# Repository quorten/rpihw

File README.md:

`rpihw` -- My First Raspberry Pi Hardware Project
=================================================

Background Info
---------------

This is my first large-scale Raspberry Pi hardware project.  The
original overly large goals of my Raspberry Pi hardware project was to
have one Raspberry Pi hardware device with all imaginable peripheral
interfaces I could ever conceivably need, so I could just plug in what
I need for a particular session.  But, since that's too large sweeping
of a goal to achieve... let's simply state what my actual design does.

This is my first iteration at designing a Raspberry Pi SPI devices
board.  The path to this real implementation started out by playing
with the Texas Instruments SN74HC595N shift register from an Arduino
parts pack.  Cool, it's an integrated circuit, but dang,
intimidating... how am I going to program this shift register?  But
then, I wired up 4 tactile switches, 1 pull-up resistor, 3 pull-down
resistors, and a 7-segment LED with decimal point.  Then... wow, I was
hooked, it's so easy and simple, and it could in theory be
daisy-chained to control an unlimited number of devices... limited
only by signal timing constraints.

I also went reading in more detail about SPI (Serial Peripheral
Interface), and I realized, hey, SPI is really just a glorified
interface to a plain old shift register integrated circuit.  I should
really try making a board that exposes some plain old shift registers
to Raspberry Pi as SPI devices.  So, that's what I started out doing.

What the main board does
------------------------

1. SPI Display/Keypad controller: 8-bit input word, 8-bit output word
   SPI device.  You program an 8-bit shift register that controls the
   display contents of one 7-segment LED digit, including decimal
   point.  An internal counter circuit automatically advances the
   current digit, so that when you write on the next cycle, you will
   set the contents of the next digit.  The input is the contents of
   one row (or column, depending on wiring) of the keyboard.  By
   reading/writing in rapid succession, you can control an 8-digit
   multiplexed LED digit display and read a 64-key keyboard.

   Technically, with one more demultiplexer chip, the circuit could
   easily be extended to a 16-digit display and a 128-key keyboard.

2. SPI motor controller: 8-bit output word SPI device.  Since this is
   an asymmetric SPI device, you must take corresponding caution when
   daisy-chaining it.  Two L293D motor controllers with some glue
   logic chips to reduce the number of bits to program them.  Can
   control up to 4 DC motors or 8 solenoids.  2 bits indicate one of 4
   states for each motor: (0) coast, (1) forward, (2) reverse, (3)
   brake.

3. Miscellaneous GPIO device control: Other single pin connections for
   controlling some LEDs, a PWM buzzer, and an arbitrary
   higher-powered device.

Of course, there is still more plenty of expansion capability for
connecting off-board SPI devices, provided that the distance is not so
long that capacitance and signaling delays becomes a problem.  In
theory, UART transceivers are an easy and cheap way to connect distant
devices to a daisy-chained SPI bus.

Oh, and I didn't even cover I2C yet.  Sure, you can populate
connectors and solder on headers for modular connection to that as you
please.

What the auxiliary boards do
----------------------------

* SPI Debug Board: a fancier, more formal recreation of my original
  breadboard design for playing with the shift register, give yourself
  a nice permanent fixture for those four buttons and the official
  connector interface I use for my SPI devices on this board design.
  Also, this is a great first time perboard project to build.

* Additional I/O connectors and device interface board: Everything
  that didn't fit on the first Eurocard perfboard that I bought, I put
  on a piece of my own "cardboard circuit board" when building the
  perfboard prototype.

Credits
-------

* Digi-Key: I used Digi-Key to prepare the Bill of Materials from my
  initial design specifications.  Also, I used the Digi-Key KiCad
  parts library when designing the formal schematics in KiCad.

* KiCad: The formal design documentation for this project is drafted
  in KiCad.  That is, anything that is not specified straight up in
  generic documentation formats like Markdown, HTML, SVG graphics,
  PDFs, spreadsheets, etc.

* UltraLibrarian: I used UltraLibrarian to get KiCad library files for
  some of the Digi-Key parts.  It's not great, and had I known in
  advance, I should have used the Digi-Key KiCad parts library for as
  many of the parts that were available over there.

* KiBoM: Some of the early versions of KiCad (if you're stuck using an
  older Debian-based distro for various odd reasons) don't have very
  nice BOM generators bundled by default, KiBoM is a fairly nice BOM
  generator to use in these cases.  It might also provide some other
  useful advanced features not in the BOM generators in the newer
  KiCad versions.

* Icarus Verilog: Open Hardware tools are not as integrated as they
  could or should be... it seems the best way to simulate digital glue
  logic is to code it up in Verilog.  Of course, this doesn't provide
  simulation for any of the analog glue connections, I'm just relying
  on careful eyeing of the schematics and best effort with my current,
  somewhat limited, design experience for that one.

N.B.: Modern versions of KiCad don't have the simple internal
autorouter, it wasn't forward ported when was Pcbnew was extensively
refactored.  That's another benefit of the older versions, if you just
want to play around with simple auto-routing because you can.  I'm
still developing this project in KiCad 4 rather than the latest
version.

Copyright Info
--------------

The rest of this project, i.e. the board design itself excluding the
library files, is in public domain via the UNLICENSE.

The Digi-Key KiCad parts library uses the Creative Commons
Share-Alike, with a special exemption that tantamounts to "fair use"
under copyright law if only bits and pieces are used for a particular
project, as opposed to most of the library.

The UltraLibrarian library parts are under proprietary copyright, but
also come with a special exemption that tantamounts to "fair use"
under copyright law if only bits and pieces are used for a particular
project, as opposed to most of the library.

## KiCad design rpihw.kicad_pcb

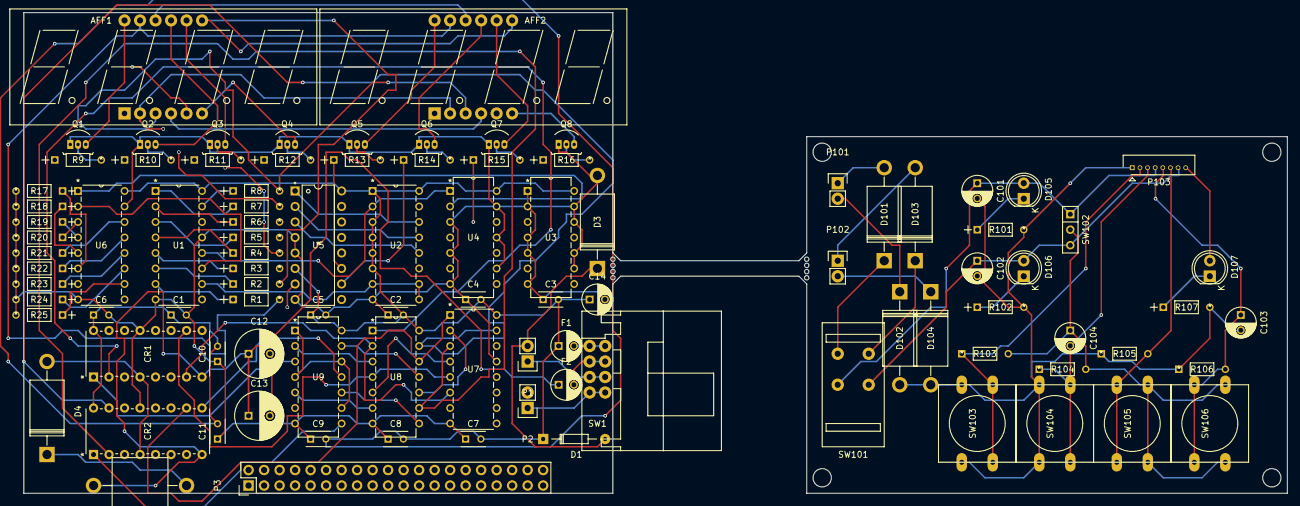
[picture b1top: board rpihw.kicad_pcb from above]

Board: 4 copper layers, 207.0 x 78.7 mm, 101 parts (0 on the bottom side), 101 nets.

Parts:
AFF1, AFF2: LDQ-N516RI; Cx56-12
C1, C2, C3, C4, C5, C6, C7, C8, C9, C10, C11: 100nF; C_Rect_L4_W2.5_P2.5
C12, C13: 220uF; C_Radial_D8_L11.5_P3.5
C14, C101, C102: 100uF; C_Radial_D5_L11_P2.5
C103: 10uF; C_Radial_D5_L11_P2.5
C104: 1uF; C_Radial_D5_L11_P2.5
CR1, CR2: L293D; PowerDIP-16
D1: 5V 9.2V; Diode_DO-35_SOD27_Horizontal_RM10
D2: 33V 53.3V; Diode_R-6_Horizontal_Unpol_RM15
D3, D4, D101, D102, D103, D104: 5A; Diode_DO-201AD_Horizontal_RM15
D105, D107: LED RED; LED-5MM
D106: LED YELW; LED-5MM
F1: 16V 2A; C_Radial_D5_L11_P2.5
F2: 60V 1.1A; C_Radial_D5_L11_P2.5
MH101, MH102, MH103, MH104: Mounting_Hole; MountingHole_3mm
P1, P2, P101, P102: CONN_01X02; Pin_Header_Straight_1x02
P3: CONN_02X20; Pin_Header_Straight_2x20
P103: CONN_01X08; Connector_Molex_PicoBlade_53047-0810
Q1, Q2, Q3, Q4, Q5, Q6, Q7, Q8: 2N3904BU; TO-92-3
R1, R2, R3, R4, R5, R6, R7, R8, R101, R102, R107: 220; STA_RNMF14
R9, R10, R11, R12, R13, R14, R15, R16: 4.7K; STA_RNMF14
R17, R18, R19, R20, R21, R22, R23, R24, R25: 51K; STA_RNMF14
R103, R104, R105: 10K; STA_RNMF14_STP
R106: 1K; STA_RNMF14_STP
SW1: DPST 6A; Hack_S201
SW101: DPST 4A; Hack_L201
SW102: SPDT 200mA; SW_Micro_SPST
SW103, SW104, SW105, SW106: SW_PUSH; SW_PUSH-12mm
U1, U7: SN74HC595N; N16
U2: SN74HC161N; N16
U3, U9: SN74HC08N; N14
U4: SN74HC04N; N14
U5: CD74HC238E; N0016A
U6: SN74HC165N; N16
U8: SN74HC32N; N14

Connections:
/RPI SPI BOARD DIP/GND_MTR: C12.2, C13.2, CR1.4, CR2.4, D4.2
/SPI 7-SEG DPLY KEYPAD CTL DIP/*RST: U1.10, U2.7, U2.9, U2.10
/SPI 7-SEG DPLY KEYPAD CTL DIP/GND: C1.2, C2.1, C3.1, C4.1, C5.2, C6.2, C7.1, C8.1, C9.1, C10.1, C11.1, C14.2, CR1.13, CR2.13, D3.2, Q1.1, Q2.1, Q3.1, Q4.1, Q5.1, Q6.1, Q7.1, Q8.1, R17.2, R18.2, R19.2, R20.2, R21.2, R22.2, R23.2, R24.2, R25.2, U1.8, U1.13, U2.8, U3.1, U3.2, U3.4, U3.5, U3.7, U3.9, U3.10, U3.12, U3.13, U4.3, U4.5, U4.7, U4.9, U4.11, U4.13, U5.4, U5.5, U5.8, U6.8, U6.15, U7.8, U7.13, U8.7, U9.7
/SPI 7-SEG DPLY KEYPAD CTL DIP/IN1: R24.1, U6.11
/SPI 7-SEG DPLY KEYPAD CTL DIP/IN2: R23.1, U6.12
/SPI 7-SEG DPLY KEYPAD CTL DIP/IN3: R22.1, U6.13
/SPI 7-SEG DPLY KEYPAD CTL DIP/IN4: R21.1, U6.14
/SPI 7-SEG DPLY KEYPAD CTL DIP/IN5: R20.1, U6.3
/SPI 7-SEG DPLY KEYPAD CTL DIP/IN6: R19.1, U6.4
/SPI 7-SEG DPLY KEYPAD CTL DIP/IN7: R18.1, U6.5
/SPI 7-SEG DPLY KEYPAD CTL DIP/IN8: R17.1, U6.6
/SPI 7-SEG DPLY KEYPAD CTL DIP/MISO_D: R25.1, U6.10
/SPI 7-SEG DPLY KEYPAD CTL DIP/SC1: R9.1, U5.15
/SPI 7-SEG DPLY KEYPAD CTL DIP/SC2: R10.1, U5.14
/SPI 7-SEG DPLY KEYPAD CTL DIP/SC3: R11.1, U5.13
/SPI 7-SEG DPLY KEYPAD CTL DIP/SC4: R12.1, U5.12
/SPI 7-SEG DPLY KEYPAD CTL DIP/SC5: R13.1, U5.11
/SPI 7-SEG DPLY KEYPAD CTL DIP/SC6: R14.1, U5.10
/SPI 7-SEG DPLY KEYPAD CTL DIP/SC7: R15.1, U5.9
/SPI 7-SEG DPLY KEYPAD CTL DIP/SC8: R16.1, U5.7
/SPI 7-SEG DPLY KEYPAD CTL DIP/SCLK: U1.11, U6.2
/SPI 7-SEG DPLY KEYPAD CTL DIP/SS: U1.12, U2.2, U4.1
/SPI 7-SEG DPLY KEYPAD CTL DIP/VCC: C1.1, C2.2, C3.2, C4.2, C5.1, C6.1, C7.2, C8.2, C9.2, C10.2, C11.2, C14.1, CR1.16, CR2.16, D1.1, F1.1, U1.16, U2.1, U2.3, U2.4, U2.5, U2.6, U2.16, U3.14, U4.14, U5.6, U5.16, U6.16, U7.16, U8.14, U9.14
/SPI MOTOR CTL DIP/PWM: U9.1, U9.4, U9.9, U9.12
/SPI MOTOR CTL DIP/VS: C12.1, C13.1, CR1.8, CR2.8, D2.1, F2.1
unnamed: AFF1.1, AFF2.1, R5.2
unnamed: AFF1.2, AFF2.2, R4.2
unnamed: AFF1.3, AFF2.3, R8.2
unnamed: AFF1.4, AFF2.4, R3.2
unnamed: AFF1.5, AFF2.5, R7.2
unnamed: AFF1.6, Q4.3
unnamed: AFF1.7, AFF2.7, R2.2
unnamed: AFF1.8, Q3.3
unnamed: AFF1.9, Q2.3
unnamed: AFF1.10, AFF2.10, R6.2
unnamed: AFF1.11, AFF2.11, R1.2
unnamed: AFF1.12, Q1.3
unnamed: AFF2.6, Q8.3
unnamed: AFF2.8, Q7.3
unnamed: AFF2.9, Q6.3
unnamed: AFF2.12, Q5.3
unnamed: C101.1, D105.2, P103.4, SW101.4, SW102.1
unnamed: C101.2, C102.2, C103.2, D102.2, D104.2, P103.1, R101.2, R102.2, R105.1, R106.1, R107.2, SW103.1, SW104.1
unnamed: C102.1, D106.2, P103.7, SW101.2, SW102.3
unnamed: C103.1, P103.5, R106.2, SW106.1
unnamed: C104.1, R103.2, R104.2, SW102.2, SW105.2, SW106.2
unnamed: C104.2, P103.3, R104.1, SW104.2
unnamed: CR1.1, U9.3
unnamed: CR1.2, U7.7, U8.1
unnamed: CR1.7, U7.6, U8.2
unnamed: CR1.9, U9.6
unnamed: CR1.10, U7.5, U8.4
unnamed: CR1.15, U7.4, U8.5
unnamed: CR2.1, U9.8
unnamed: CR2.2, U7.3, U8.9
unnamed: CR2.7, U7.2, U8.10
unnamed: CR2.9, U9.11
unnamed: CR2.10, U7.1, U8.12
unnamed: CR2.15, U7.15, U8.13
unnamed: D1.2, D3.1, P1.2
unnamed: D2.2, D4.1, P2.2
unnamed: D101.1, SW101.3
unnamed: D101.2, P101.1
unnamed: D102.1, P101.2
unnamed: D103.1, SW101.1
unnamed: D103.2, P102.1
unnamed: D104.1, P102.2
unnamed: D105.1, R101.1
unnamed: D106.1, R102.1
unnamed: D107.1, R107.1
unnamed: D107.2, P103.8
unnamed: F1.2, SW1.4
unnamed: F2.2, SW1.2
unnamed: P1.1, SW1.3
unnamed: P2.1, SW1.1
unnamed: P103.2, R103.1, SW103.2
unnamed: P103.6, R105.2, SW105.1
unnamed: Q1.2, R9.2
unnamed: Q2.2, R10.2
unnamed: Q3.2, R11.2
unnamed: Q4.2, R12.2
unnamed: Q5.2, R13.2
unnamed: Q6.2, R14.2
unnamed: Q7.2, R15.2
unnamed: Q8.2, R16.2
unnamed: R1.1, U1.7
unnamed: R2.1, U1.6
unnamed: R3.1, U1.5
unnamed: R4.1, U1.4
unnamed: R5.1, U1.3
unnamed: R6.1, U1.2
unnamed: R7.1, U1.1
unnamed: R8.1, U1.15
unnamed: U2.12, U5.3
unnamed: U2.13, U5.2
unnamed: U2.14, U5.1
unnamed: U4.2, U6.1
unnamed: U8.3, U9.2
unnamed: U8.6, U9.5
unnamed: U8.8, U9.10
unnamed: U8.11, U9.13

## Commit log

2020-07-14 Many small improvements.
    * Move to V1.1 using less glue logic in the 7-seg display controller.
    * Complete perfboard wiring diagram, show in layers.
    * Minor spelling error and formatting improvements.
2020-07-14 Add auto-routed PCB traces just because we can.
    Note that my placeholder switch pad footprints are bad and will need to
    be replaced with ones that have the actual numbers for all 4 pins.
2020-07-16 Add basic 3D models for switches, needs improvement.
    These 3D models were redrawn from the datasheet technical drawings.
2020-07-16 Add DocLib info for UltraLibrarian parts because we can.
    Also add Digi-Key fields to the UltraLibrarian parts.
2020-07-17 Improve switch footprints, add beveled 3D model.
2020-07-17 Silk screen layer improvements.
2020-07-17 Minor changes to layering in perfboard wiring diagram.
    This will better allow for indecisiveness/upgrades on interlaced
    digit scan on the 7-segment LED display.
2020-07-17 Improve footprint hole diameters, add DO-201AD 3D model.
    Also use two-sided layers setup since through-hole boards need solder
    mask on both sides.
2020-07-17 Better silkscreen, footprint corrections.
2020-07-19 Improve footprints, add 3D model for big TVS diode.
    Whoops, I didn't checkin the earlier revision switch footprints, those
    revisions will be broken unfortunately.
2020-07-19 Wiring diagram I/O connector improvement.
2020-07-20 Fix traces.
2020-07-30 Wiring diagram updates.
2020-10-19 Use thermistor schematic for PTC resettable fuse.
2020-11-29 Add Icarus Verilog based simulation of the glue logic.
    Also update some minor issues made with the wiring labeling, and update
    the perboard construction wiring guide.
2020-11-29 Add Icarus Verilog files to .gitignore, note tool in README.md.

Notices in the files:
parts and their libraries:
Copyright 2016 Accelerated Designs. All rights reserved.
